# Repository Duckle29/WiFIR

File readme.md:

# WiFI*R*

The WiFI*R* is a WiFi IR blaster / remote, based around a WeMos D1 mini (ESP8266)

[Firmware](https://github.com/Duckle29/wifir_firmware)  
The WiFIR was made from a need to control a heatpump / ac to allow pre-heating of a summer-house before arriving. It can however control anything IR controlled.

[Interactive BOM](https://WiFIR.github.io/pcb/ibom.html)

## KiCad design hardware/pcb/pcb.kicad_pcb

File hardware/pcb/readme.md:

# Duckles generic PCB template

This is the WiFIR. It's basically a battery operated wifi IR-blaster. It's intended to remote-control a heat-pump to heat up a house in advance. More details later :)

[Interactive BOM](duckle29.github.io/WiFIR/hardware/pcb/ibom.html)

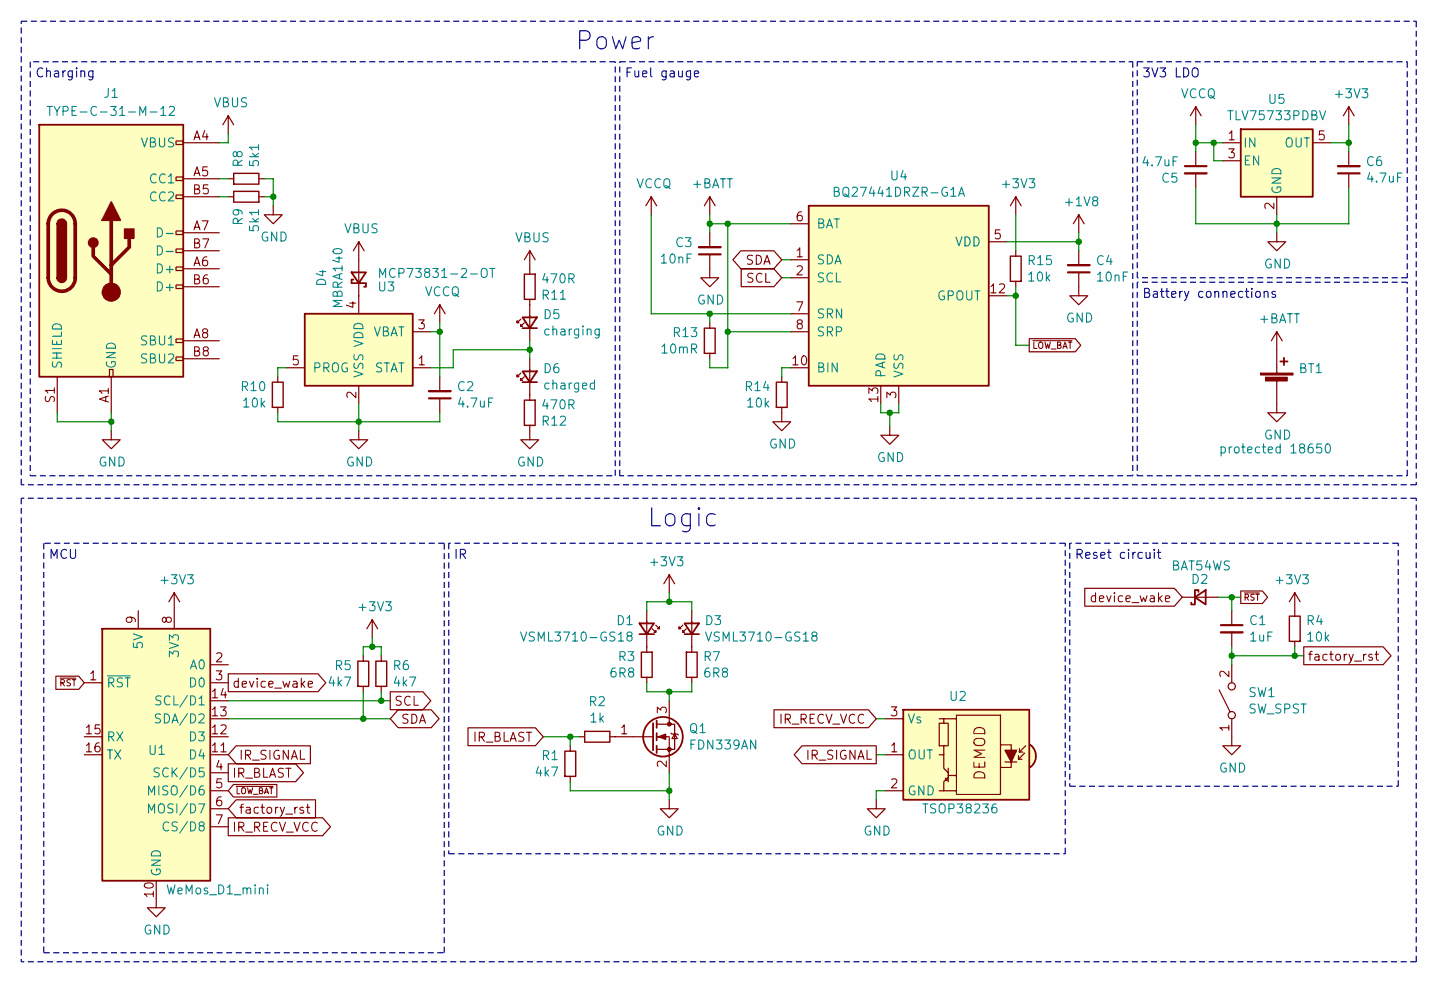
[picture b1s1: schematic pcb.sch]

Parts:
BT1: protected 18650; BatteryHolder_Keystone_1042_1x18650
C1: 1uF; C_0603_1608Metric_Pad1.05x0.95mm_HandSolder
C2, C5, C6: 4.7uF; C_0805_2012Metric_Pad1.15x1.40mm_HandSolder
C3, C4: 10nF; C_0603_1608Metric_Pad1.05x0.95mm_HandSolder
D1, D3: VSML3710-GS18; LED_PLCC-2
D2: BAT54WS; D_SOD-323_HandSoldering
D4: MBRA140; D_SMA
D5: charging; LED_0603_1608Metric_Pad1.05x0.95mm_HandSolder
D6: charged; LED_0603_1608Metric_Pad1.05x0.95mm_HandSolder
J1: TYPE-C-31-M-12; USB_C_Receptacle_HRO_TYPE-C-31-M-12
Q1: FDN339AN; SOT-23_Handsoldering
R1, R5, R6: 4k7; R_0603_1608Metric_Pad1.05x0.95mm_HandSolder
R2: 1k; R_0603_1608Metric_Pad1.05x0.95mm_HandSolder
R3, R7: 6R8; R_0603_1608Metric_Pad1.05x0.95mm_HandSolder
R4, R10, R14, R15: 10k; R_0603_1608Metric_Pad1.05x0.95mm_HandSolder
R8, R9: 5k1; R_0603_1608Metric_Pad1.05x0.95mm_HandSolder
R11, R12: 470R; R_0603_1608Metric_Pad1.05x0.95mm_HandSolder
R13: 10mR; R_0603_1608Metric_Pad1.05x0.95mm_HandSolder
SW1: SW_SPST; SW_Push_1P1T_NO_6x6mm_H9.5mm
U1: WeMos_D1_mini; WEMOS_D1_mini_light
U2: TSOP38236; Vishay_MINICAST-3Pin
U3: MCP73831-2-OT; SOT-23-5
U4: BQ27441DRZR-G1A; Texas_S-PDSO-N12
U5: TLV75733PDBV; SOT-23-5

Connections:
+1V8: C4.2, U4.5 (VDD)
+3V3: C6.2, D1.2 (A), D3.2 (A), R4.2, R5.2, R6.2, R15.2, U1.8 (3V3), U5.5 (OUT)
+BATT: BT1.1 (+), C3.2, R13.1, U4.6 (BAT), U4.8 (SRP)
GND: BT1.2 (-), C2.1, C3.1, C4.1, C5.2, C6.1, J1.A1 (GND), J1.A12 (GND), J1.B1 (GND), J1.B12 (GND), J1.S1 (SHIELD), Q1.2 (S), R1.1, R8.2, R9.1, R10.1, R12.2, R14.1, SW1.1 (A), U1.10 (GND), U2.2 (GND), U3.2 (VSS), U4.3 (VSS), U4.13 (PAD), U5.2 (GND)
IR_BLAST: R1.2, R2.1, U1.4 (SCK/D5)
IR_RECV_VCC: U1.7 (CS/D8), U2.3 (Vs)
IR_SIGNAL: U1.11 (D4), U2.1 (OUT)
unnamed: D1.1 (K), R3.1
unnamed: D3.1 (K), R7.1
unnamed: D4.1 (K), U3.4 (VDD)
unnamed: D5.1 (K), D6.2 (A), U3.1 (STAT)
unnamed: D5.2 (A), R11.2
unnamed: D6.1 (K), R12.1
unnamed: J1.A5 (CC1), R8.1
unnamed: J1.B5 (CC2), R9.2
unnamed: Q1.1 (G), R2.2
unnamed: Q1.3 (D), R3.2, R7.2
unnamed: R10.2, U3.5 (PROG)
unnamed: R14.2, U4.10 (BIN)
SCL: R6.1, U1.14 (SCL/D1), U4.2 (SCL)
SDA: R5.1, U1.13 (SDA/D2), U4.1 (SDA)
VBUS: D4.2 (A), J1.A4 (VBUS), J1.A9 (VBUS), J1.B4 (VBUS), J1.B9 (VBUS), R11.1
VCCQ: C2.2, C5.1, R13.2, U3.3 (VBAT), U4.7 (SRN), U5.1 (IN), U5.3 (EN)
device_wake: D2.1 (K), U1.3 (D0)
factory_rst: C1.2, R4.1, SW1.2 (B), U1.6 (MOSI/D7)
~LOW_BAT: R15.1, U1.5 (MISO/D6), U4.12 (GPOUT)
~RST: C1.1, D2.2 (A), U1.1 (~RST)

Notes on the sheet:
Logic
Power
3V3 LDO
Fuel gauge
Charging
MCU
Reset circuit
Battery connections

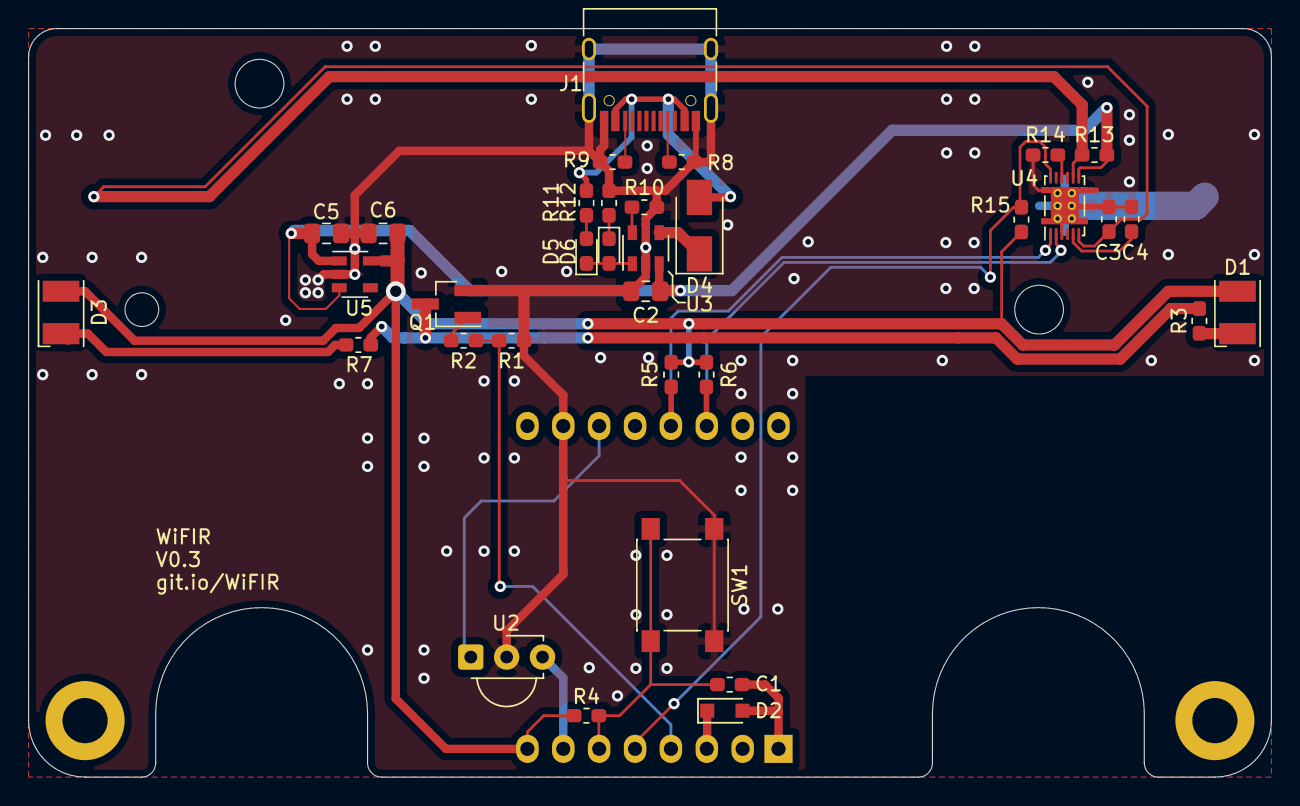
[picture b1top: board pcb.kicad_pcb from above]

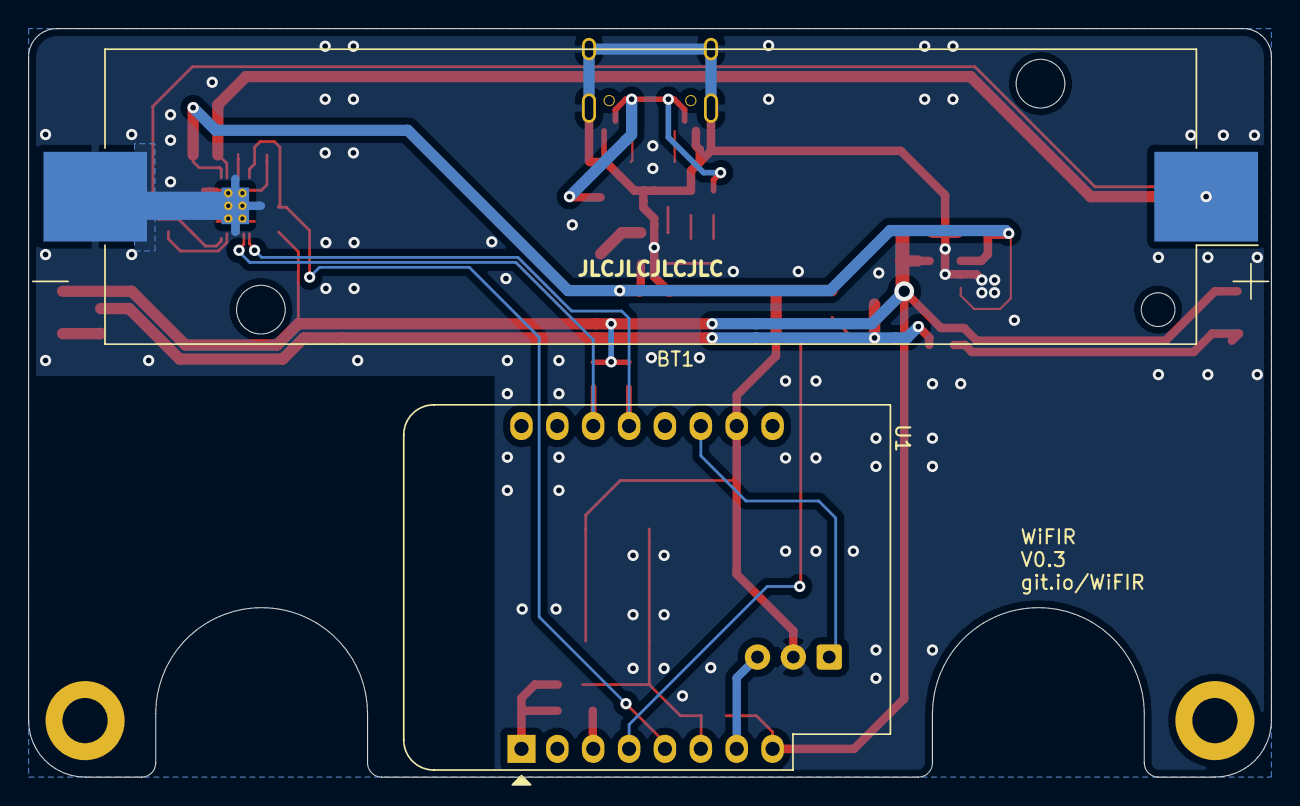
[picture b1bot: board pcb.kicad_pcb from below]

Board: 2 copper layers, 88.0 x 53.0 mm, 36 parts (2 on the bottom side), 27 nets.

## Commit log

2020-03-16 updated renders
2020-03-21 Moved BQ fuelgauge to battery gnd terminal for thermal coupling
2020-03-21 Moved docs to root folder
2020-03-21 Moved readme up to root folder
2020-03-22 Updated renders to match V2
2020-03-22 Added gerbers
2020-03-22 saved pcbnew
2020-03-22 Added readme to firmware
2020-03-22 Added schematic
2020-03-22 Fixed readme header
2020-03-24 Added case for v0.2
2020-03-24 Centered USB-C, Added cutouts for 15mm case posts
2020-04-15 Added MQTT lib
